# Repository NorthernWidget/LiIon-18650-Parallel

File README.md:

# Parallel-LiIon-18650
Lithium-ion 18650 battery power supply: PCB

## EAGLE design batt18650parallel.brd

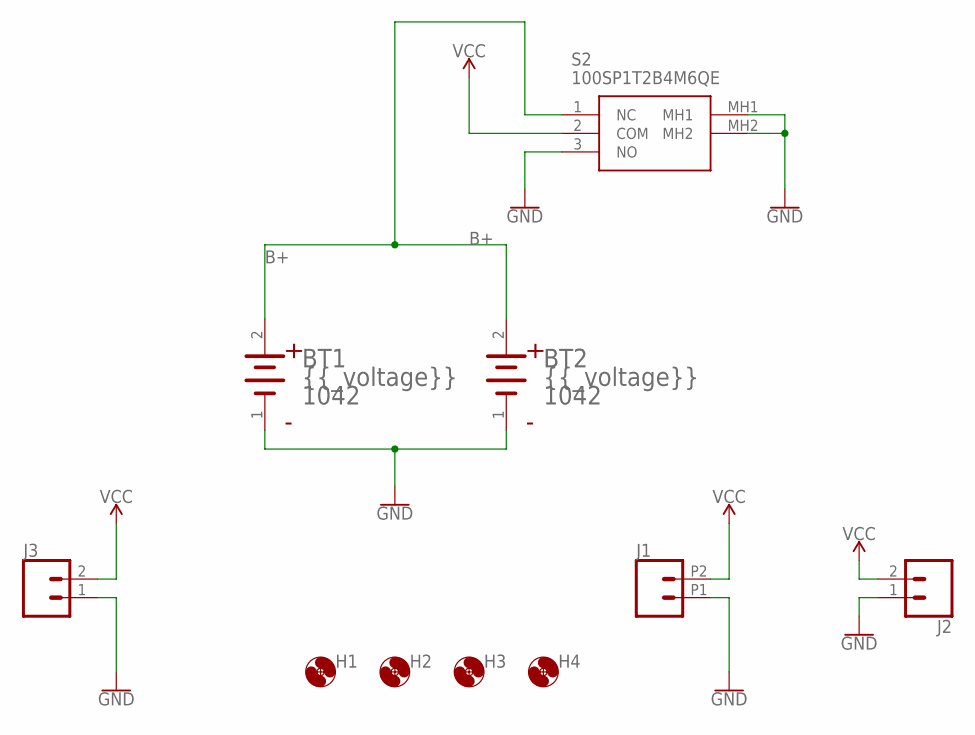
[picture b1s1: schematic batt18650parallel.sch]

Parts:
BT1, BT2: KEYSTONE_1042KEYSTONE_1042_0_0; KEYSTONE_1042_0
H1, H2, H3, H4: MOUNTING_HOLE4_NP; 4_40
J1: CONN_022.54_SCREW_ROUND; 1X02_2.54_SCREWTERM_ROUND
J2: CONN_02-JST-2MM-SMT; JST-2-SMD
J3: CONN_023.5MM_ROUND; SCREWTERMINAL-3.5MM-2_ROUND
S2: 100SP1T2B4M6QE

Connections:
B+: BT1.2 (ANODE), BT2.2 (ANODE), S2.1 (NC)
GND: BT1.1 (CATHODE), BT2.1 (CATHODE), J1.P1 (1), J2.1 (2), J3.1, S2.3 (NO), S2.MH1, S2.MH2
VCC: J1.P2 (2), J2.2 (1), J3.2, S2.2 (COM)

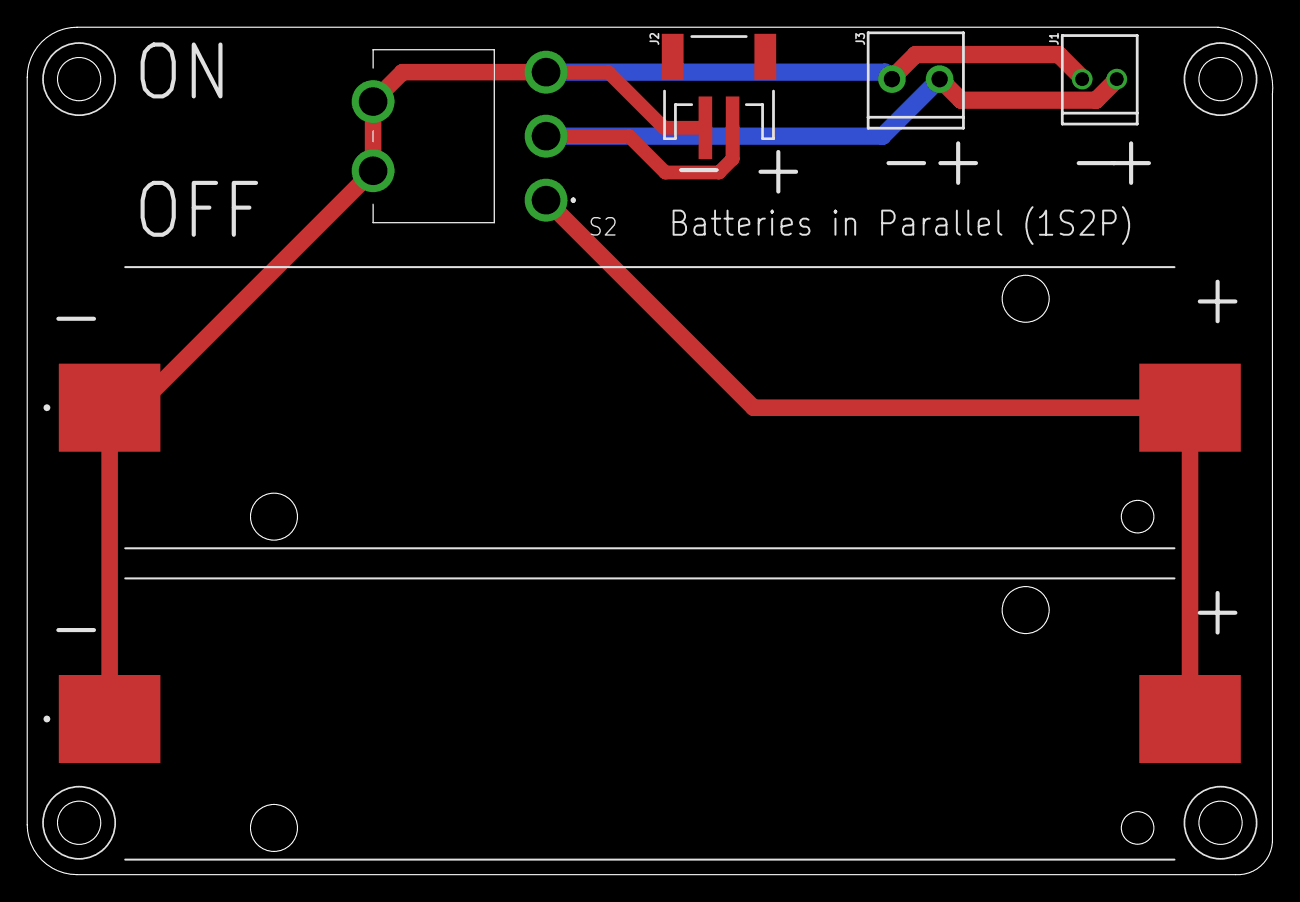
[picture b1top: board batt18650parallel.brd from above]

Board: 2 copper layers, 91.5 x 62.2 mm, 10 parts (0 on the bottom side), 3 nets.

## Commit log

2020-02-04 CC-BY-SA
2020-02-04 First draft
2020-02-05 Bobby Schulz design review: address
2020-02-05 Minor updates to connector orientation, pad shape
2020-02-05 Updated part BoM info

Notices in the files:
parts and their libraries:
SparkFun-PowerSymbols: Licensing: Creative Commons ShareAlike 4.0 International - https://creativecommons.org/licenses/by-sa/4.0
